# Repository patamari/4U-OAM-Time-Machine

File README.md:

# 4U-OAM-Time-Machine
4U port of the Olivia Artz Modular Time Machine + the Timo Rozendal expander combined into one board. LW format module.
CC-BY-NC-SA

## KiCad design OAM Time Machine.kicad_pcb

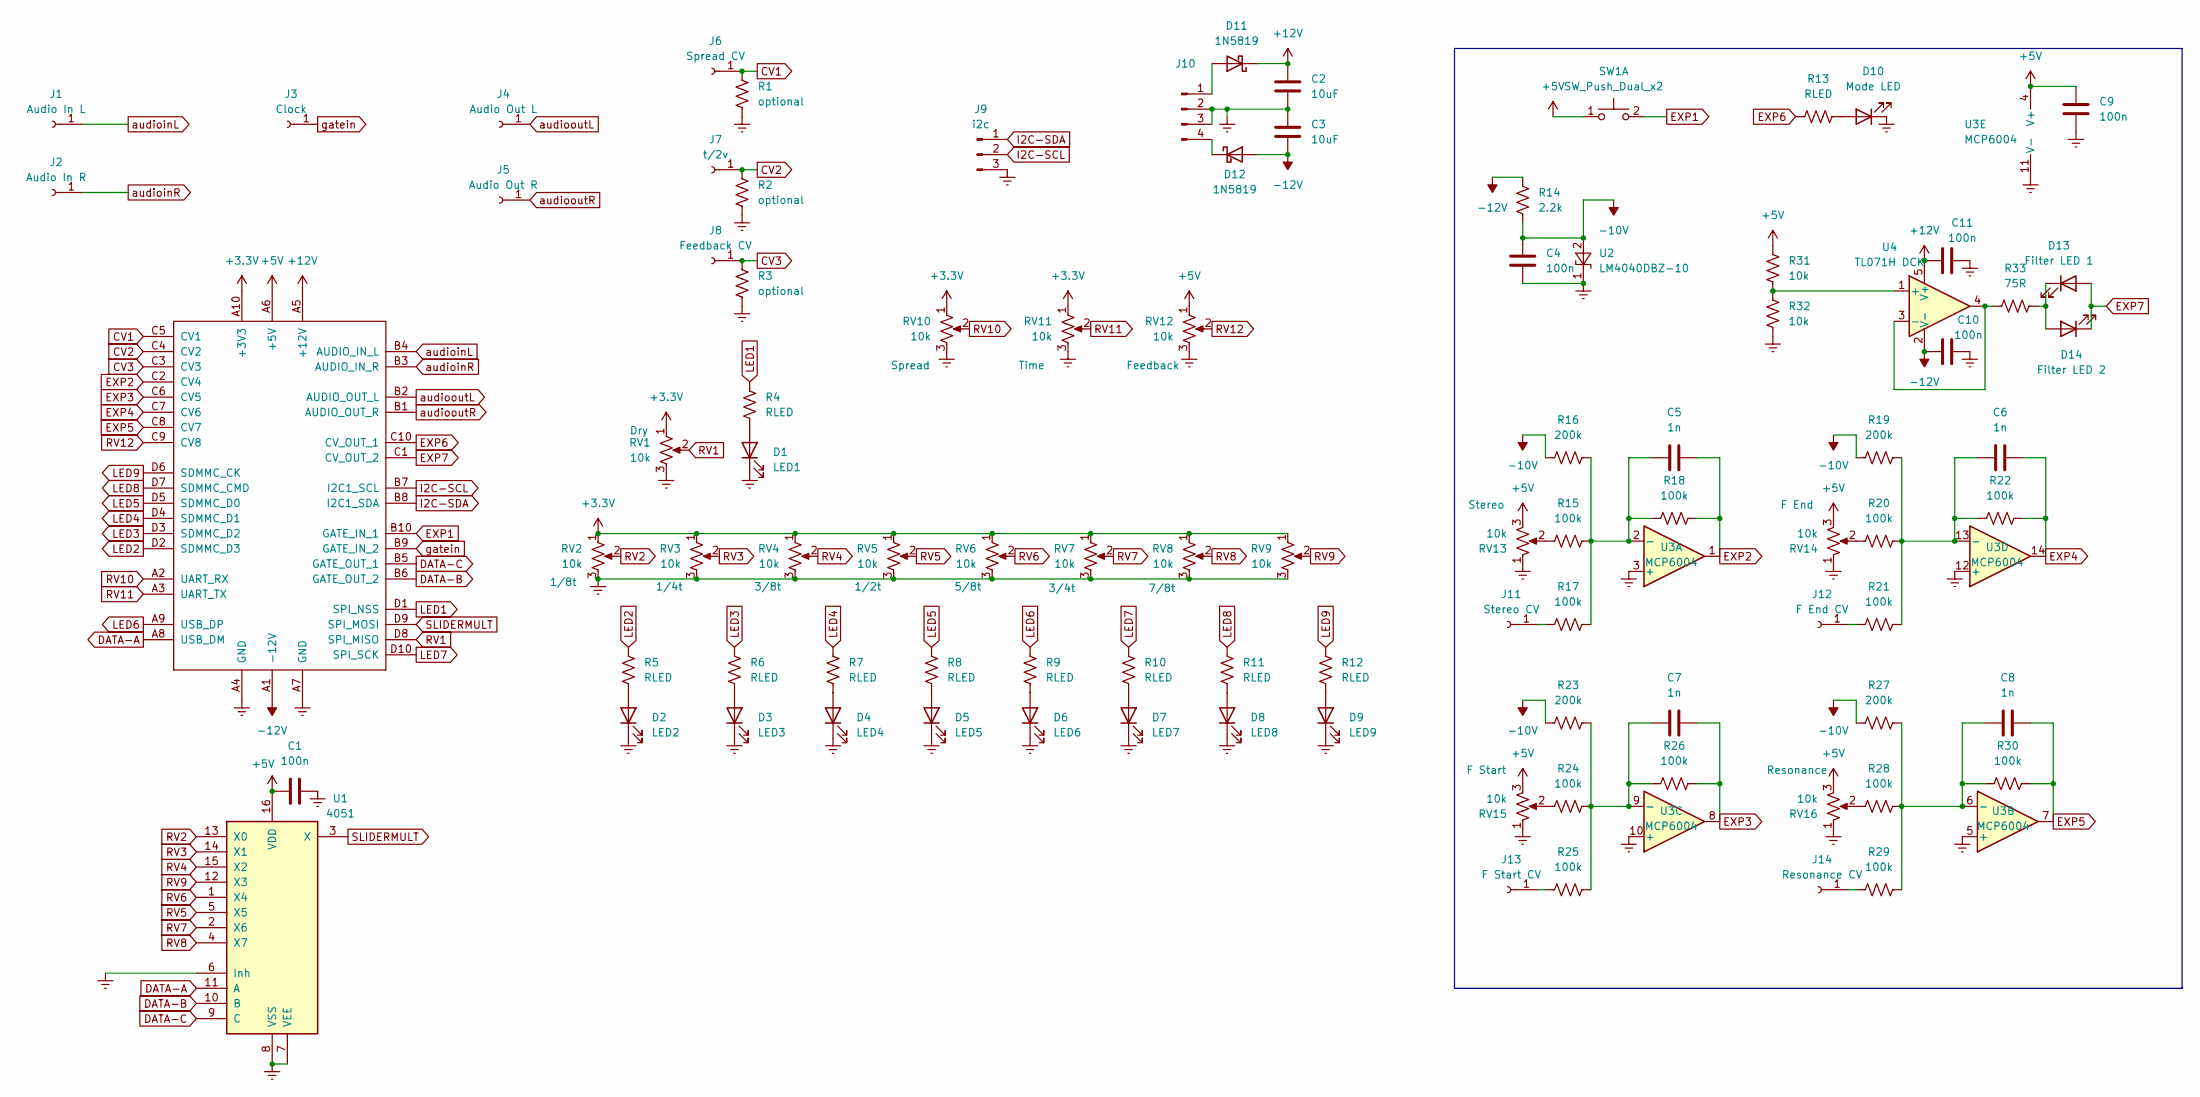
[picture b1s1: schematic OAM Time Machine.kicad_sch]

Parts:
C1, C4, C9, C10, C11: 100n; C_0805_2012Metric_Pad1.18x1.45mm_HandSolder
C2, C3: 10uF; C_0805_2012Metric_Pad1.18x1.45mm_HandSolder
C5, C6, C7, C8: 1n; C_0805_2012Metric_Pad1.18x1.45mm_HandSolder
D1: LED1; LED_D3.0mm
D2: LED2; LED_D3.0mm
D3: LED3; LED_D3.0mm
D4: LED4; LED_D3.0mm
D5: LED5; LED_D3.0mm
D6: LED6; LED_D3.0mm
D7: LED7; LED_D3.0mm
D8: LED8; LED_D3.0mm
D9: LED9; LED_D3.0mm
D10: Mode LED; LED_D3.0mm
D11, D12: 1N5819; D_SOD-123
D13: Filter LED 1; LED_D3.0mm
D14: Filter LED 2; LED_D3.0mm
J1: Audio In L; BananaJackHookup
J2: Audio In R; BananaJackHookup
J3: Clock; BananaJackHookup
J4: Audio Out L; BananaJackHookup
J5: Audio Out R; BananaJackHookup
J6: Spread CV; BananaJackHookup
J7: t/2v; BananaJackHookup
J8: Feedback CV; BananaJackHookup
J9: i2c; PinSocket_1x03_P2.54mm_Vertical
J10: Conn_01x04_Pin; Molex_KK-254_AE-6410-04A_1x04_P2.54mm_Vertical
J11: Stereo CV; BananaJackHookup
J12: F End CV; BananaJackHookup
J13: F Start CV; BananaJackHookup
J14: Resonance CV; BananaJackHookup
PATCH1: ES_DAISY_PATCH_SM_REV1; DAISY_PATCH_SM
R1, R2, R3: optional; R_0805_2012Metric_Pad1.20x1.40mm_HandSolder
R4, R5, R6, R7, R8, R9, R10, R11, R12, R13: RLED; R_0805_2012Metric_Pad1.20x1.40mm_HandSolder
R14: 2.2k; R_0805_2012Metric_Pad1.20x1.40mm_HandSolder
R15, R17, R18, R20, R21, R22, R24, R25, R26, R28, R29, R30: 100k; R_0805_2012Metric_Pad1.20x1.40mm_HandSolder
R16, R19, R23, R27: 200k; R_0805_2012Metric_Pad1.20x1.40mm_HandSolder
R31, R32: 10k; R_0805_2012Metric_Pad1.20x1.40mm_HandSolder
R33: 75R; R_0805_2012Metric_Pad1.20x1.40mm_HandSolder
RV1, RV2, RV3, RV4, RV5, RV6, RV7, RV8, RV9, RV10, RV11, RV12, RV13, RV14, RV15, RV16: 10k; Alpha Pot
SW1: SW_Push_Dual_x2; SW_PUSH_6mm
U1: 4051; SOIC-16_3.9x9.9mm_P1.27mm
U2: LM4040DBZ-10; SOT-23
U3: MCP6004; SOIC-14_3.9x8.7mm_P1.27mm
U4: TL071H DCK; SOT-353_SC-70-5_Handsoldering

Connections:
+3.3V: PATCH1.A10 (+3V3), RV1.1, RV2.1, RV3.1, RV4.1, RV5.1, RV6.1, RV7.1, RV8.1, RV9.1, RV10.1, RV11.1
+5V: C1.1, C9.2, PATCH1.A6 (+5V), R31.1, RV12.1, RV13.3, RV14.3, RV15.3, RV16.3, SW1.1 (C), U1.16 (VDD), U3.4 (V+)
+12V: C2.1, C11.2, D11.1 (K), PATCH1.A5 (+12V), U4.5 (V+)
-10V: C4.2, R14.2, R16.1, R19.1, R23.1, R27.1, U2.2 (A)
-12V: C3.2, C10.2, D12.2 (A), PATCH1.A1 (-12V), R14.1, U4.2 (V-)
CV1: J6.1, PATCH1.C5 (CV1), R1.1
CV2: J7.1, PATCH1.C4 (CV2), R2.1
CV3: J8.1, PATCH1.C3 (CV3), R3.1
DATA-A: PATCH1.A8 (USB_DM), U1.11 (A)
DATA-B: PATCH1.B6 (GATE_OUT_2), U1.10 (B)
DATA-C: PATCH1.B5 (GATE_OUT_1), U1.9 (C)
EXP1: PATCH1.B10 (GATE_IN_1), SW1.2 (D)
EXP2: C5.1, PATCH1.C2 (CV4), R18.2, U3.1
EXP3: C7.1, PATCH1.C6 (CV5), R26.2, U3.8
EXP4: C6.1, PATCH1.C7 (CV6), R22.2, U3.14
EXP5: C8.1, PATCH1.C8 (CV7), R30.2, U3.7
EXP6: PATCH1.C10 (CV_OUT_1), R13.1
EXP7: D13.2 (A), D14.1 (K), PATCH1.C1 (CV_OUT_2)
GNDREF: C1.2, C2.2, C3.1, C4.1, C9.1, C10.1, C11.1, D1.1 (K), D2.1 (K), D3.1 (K), D4.1 (K), D5.1 (K), D6.1 (K), D7.1 (K), D8.1 (K), D9.1 (K), D10.1 (K), J9.3, J10.2, J10.3, PATCH1.A4 (GND), PATCH1.A7 (GND), R1.2, R2.2, R3.2, R32.2, RV1.3, RV2.3, RV3.3, RV4.3, RV5.3, RV6.3, RV7.3, RV8.3, RV9.3, RV10.3, RV11.3, RV12.3, RV13.1, RV14.1, RV15.1, RV16.1, U1.6 (Inh), U1.7 (VEE), U1.8 (VSS), U2.1 (K), U3.3 (+), U3.5 (+), U3.10 (+), U3.11 (V-), U3.12 (+)
I2C-SCL: J9.2, PATCH1.B7 (I2C1_SCL)
I2C-SDA: J9.1, PATCH1.B8 (I2C1_SDA)
LED1: PATCH1.D1 (SPI_NSS), R4.1
LED2: PATCH1.D2 (SDMMC_D3), R5.1
LED3: PATCH1.D3 (SDMMC_D2), R6.1
LED4: PATCH1.D4 (SDMMC_D1), R7.1
LED5: PATCH1.D5 (SDMMC_D0), R8.1
LED6: PATCH1.A9 (USB_DP), R9.1
LED7: PATCH1.D10 (SPI_SCK), R10.1
LED8: PATCH1.D7 (SDMMC_CMD), R11.1
LED9: PATCH1.D6 (SDMMC_CK), R12.1
unnamed: D1.2 (A), R4.2
unnamed: D2.2 (A), R5.2
unnamed: D3.2 (A), R6.2
unnamed: D4.2 (A), R7.2
unnamed: D5.2 (A), R8.2
unnamed: D6.2 (A), R9.2
unnamed: D7.2 (A), R10.2
unnamed: D8.2 (A), R11.2
unnamed: D9.2 (A), R12.2
unnamed: D10.2 (A), R13.2
unnamed: D11.2 (A), J10.1
unnamed: D12.1 (K), J10.4
unnamed: D13.1 (K), D14.2 (A), R33.1
unnamed: J11.1, R17.1
unnamed: J12.1, R21.1
unnamed: J13.1, R25.1
unnamed: J14.1, R29.1
unnamed: R15.1, RV13.2
unnamed: R20.1, RV14.2
unnamed: R24.1, RV15.2
unnamed: R28.1, RV16.2
unnamed: C5.2, R15.2, R16.2, R17.2, R18.1, U3.2 (-)
unnamed: C8.2, R27.2, R28.2, R29.2, R30.1, U3.6 (-)
unnamed: C7.2, R23.2, R24.2, R25.2, R26.1, U3.9 (-)
unnamed: C6.2, R19.2, R20.2, R21.2, R22.1, U3.13 (-)
unnamed: R31.2, R32.1, U4.1 (+)
unnamed: R33.2, U4.3 (-), U4.4
RV1: PATCH1.D8 (SPI_MISO), RV1.2
RV2: RV2.2, U1.13 (X0)
RV3: RV3.2, U1.14 (X1)
RV4: RV4.2, U1.15 (X2)
RV5: RV5.2, U1.5 (X5)
RV6: RV6.2, U1.1 (X4)
RV7: RV7.2, U1.2 (X6)
RV8: RV8.2, U1.4 (X7)
RV9: RV9.2, U1.12 (X3)
RV10: PATCH1.A2 (UART_RX), RV10.2
RV11: PATCH1.A3 (UART_TX), RV11.2
RV12: PATCH1.C9 (CV8), RV12.2
SLIDERMULT: PATCH1.D9 (SPI_MOSI), U1.3 (X)
audioinL: J1.1, PATCH1.B4 (AUDIO_IN_L)
audioinR: J2.1, PATCH1.B3 (AUDIO_IN_R)
audiooutL: J4.1, PATCH1.B2 (AUDIO_OUT_L)
audiooutR: J5.1, PATCH1.B1 (AUDIO_OUT_R)
gatein: J3.1, PATCH1.B9 (GATE_IN_2)

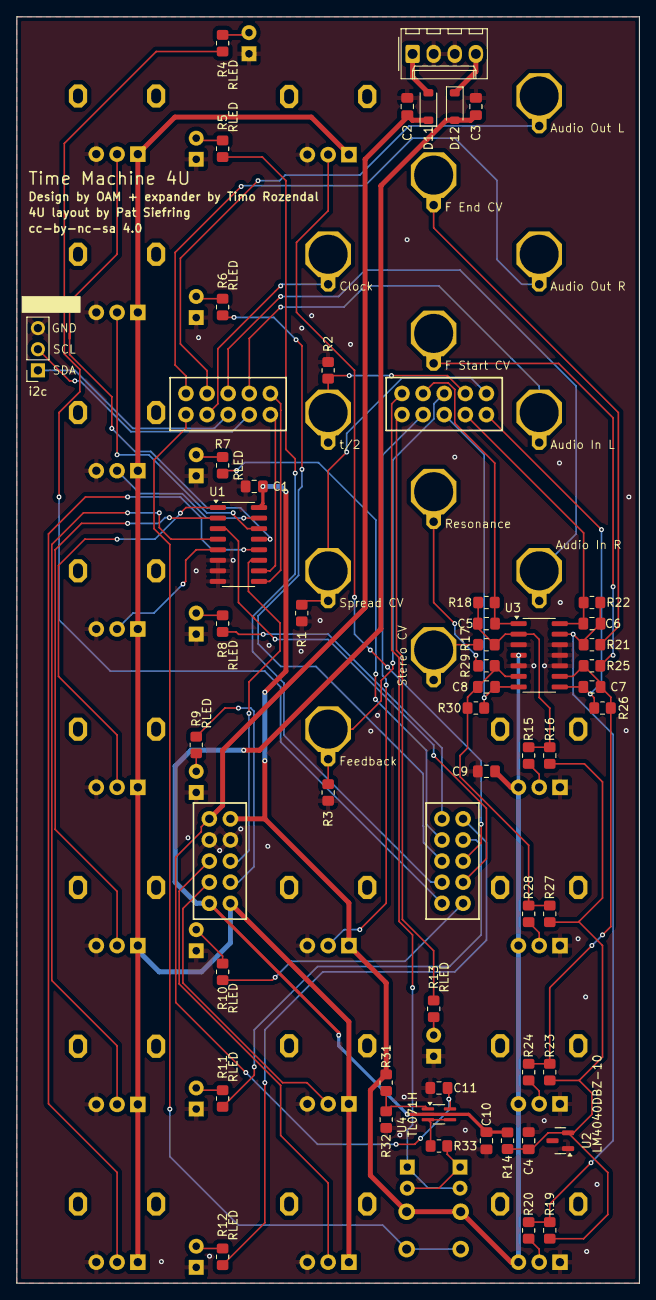
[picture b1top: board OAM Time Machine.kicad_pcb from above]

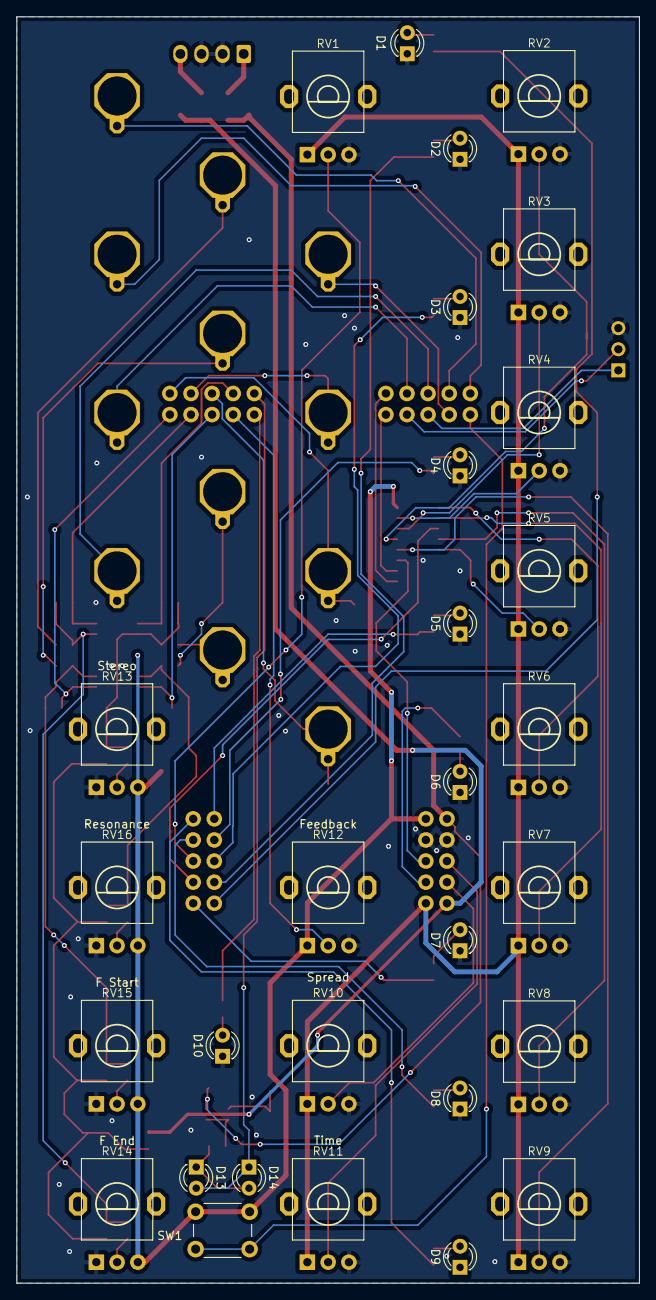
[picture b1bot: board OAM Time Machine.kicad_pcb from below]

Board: 2 copper layers, 74.9 x 152.4 mm, 94 parts (29 on the bottom side), 75 nets.

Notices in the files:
OAM Time Machine.kicad_pcb:
cc-by-nc-sa 4.0
